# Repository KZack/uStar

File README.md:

# uStar
uStar Files and Documents

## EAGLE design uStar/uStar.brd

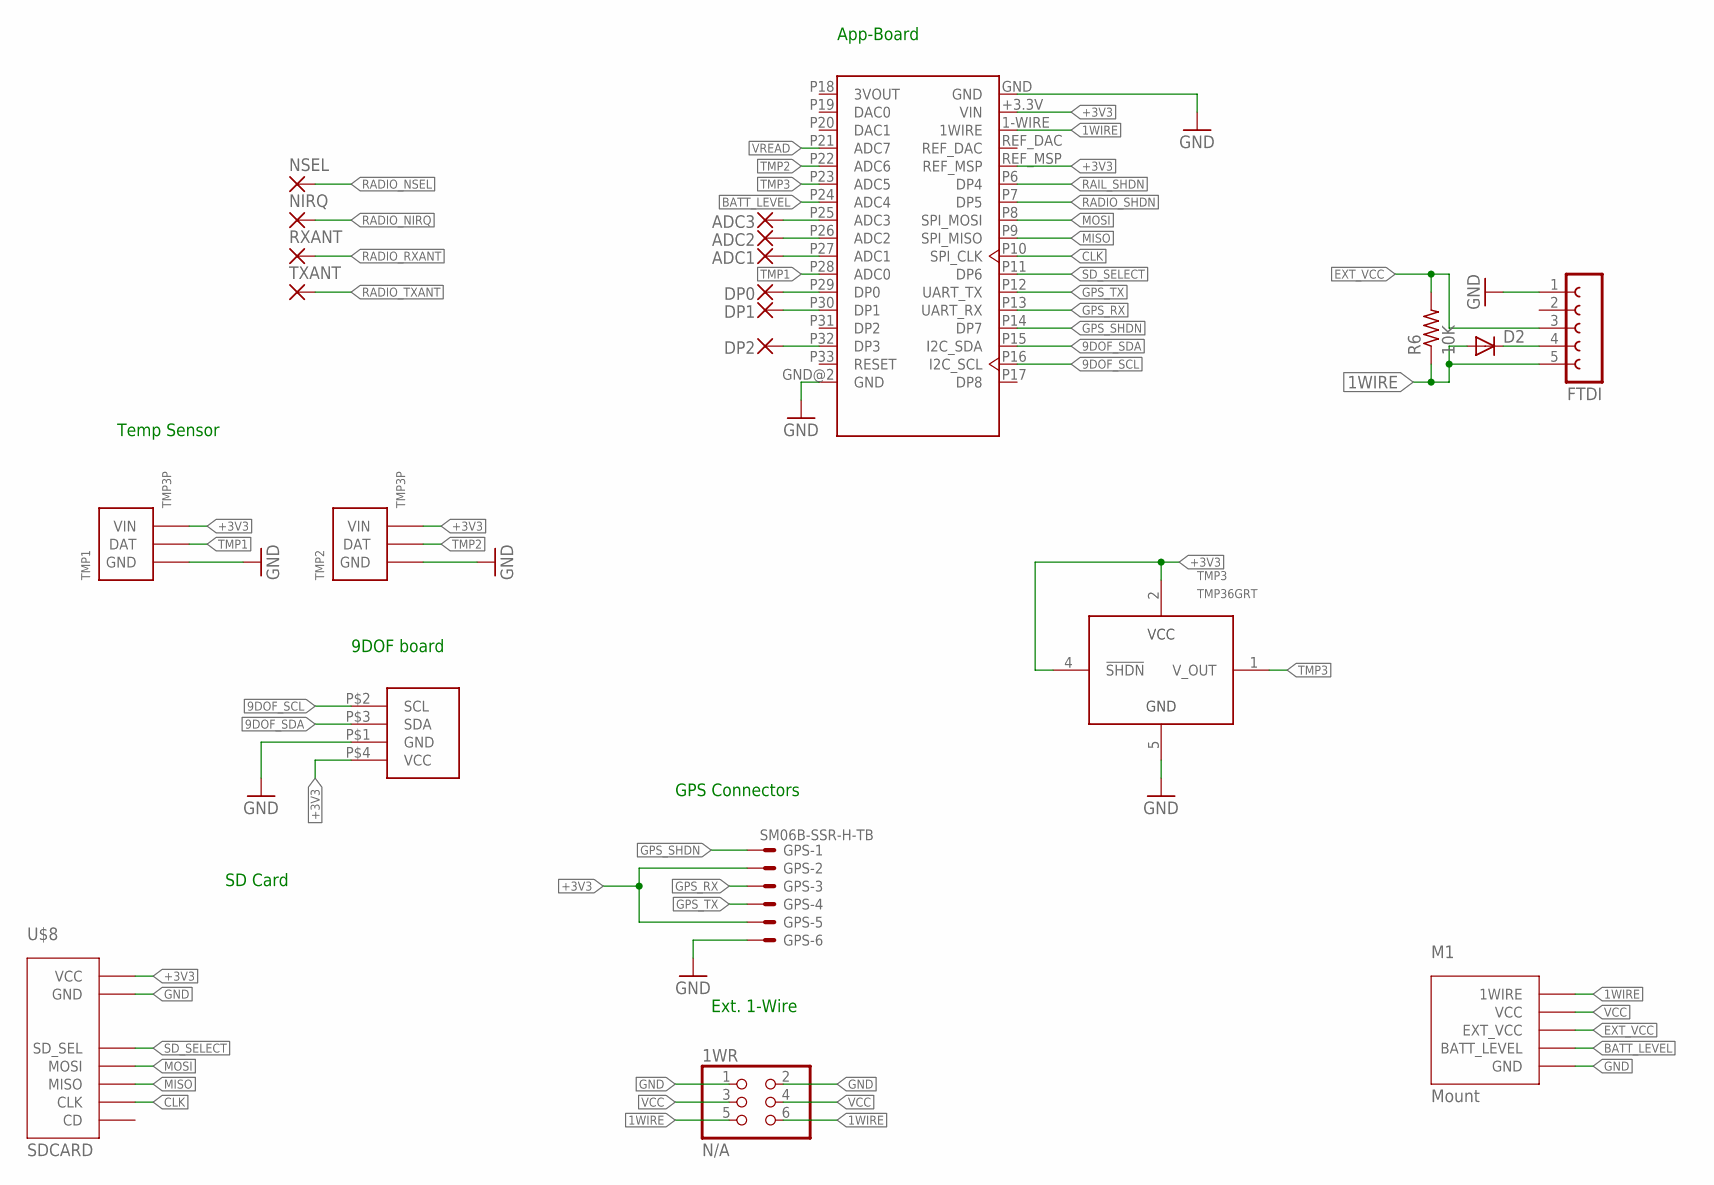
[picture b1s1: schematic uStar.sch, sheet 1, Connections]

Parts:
1WR: N/A; 2X03
ADC1, ADC2, ADC3: 1,6/0,9
D2: D-B260A; SMA-DO214AC
DP0, DP1, DP2: 1,6/0,9
FTDI: FE05-1
GPS: SM06B-SSR-H-TB
M1: Mount; 4X8MOUNT
NIRQ: 1,6/0,9
NSEL: 1,6/0,9
R6: 10K; R0603
RXANT: 1,6/0,9
TMP1, TMP2: TMP3P
TMP3: TMP36GRT; SOT-23-5
TXANT: 1,6/0,9
U$1: App-Board 1.2/1.3; APPCORE_RECEIVER
U$5: 9DOF
U$8: SDCARD

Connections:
1WIRE: 1WR.5, 1WR.6, D2.A, FTDI.5, M1.P$2 (1WIRE), M1.P$5 (1WIRE), R6.1, U$1.1-WIRE (1WIRE)
9DOF_SCL: U$1.P16 (I2C_SCL), U$5.P$2 (SCL)
9DOF_SDA: U$1.P15 (I2C_SDA), U$5.P$3 (SDA)
+3V3: GPS.2, GPS.5, TMP1.P$3 (VIN), TMP2.P$3 (VIN), TMP3.2 (VCC), TMP3.4 (!SHDN), U$1.+3.3V (VIN), U$1.REF_MSP, U$5.P$4 (VCC), U$8.P$3 (VCC); also elsewhere on the board
BATT_LEVEL: M1.P$6 (BATT_LEVEL), U$1.P24 (ADC4)
CLK: U$1.P10 (SPI_CLK), U$8.P$4 (CLK); also elsewhere on the board
EXT_VCC: FTDI.3, M1.P$3 (EXT_VCC), R6.2; also elsewhere on the board
GND: 1WR.1, 1WR.2, FTDI.1, GPS.6, M1.P$1 (GND), M1.P$8 (GND), TMP1.P$1 (GND), TMP2.P$1 (GND), TMP3.5 (GND), U$1.GND, U$1.GND@2 (GND), U$5.P$1 (GND), U$8.P$5 (GND); also elsewhere on the board
GPS_RX: GPS.3, U$1.P13 (UART_RX)
GPS_SHDN: GPS.1, U$1.P14 (DP7)
GPS_TX: GPS.4, U$1.P12 (UART_TX)
MISO: U$1.P9 (SPI_MISO), U$8.P$6 (MISO); also elsewhere on the board
MOSI: U$1.P8 (SPI_MOSI), U$8.P$2 (MOSI); also elsewhere on the board
unnamed: D2.K (C), FTDI.4
unnamed: ADC1.1, U$1.P27 (ADC1)
unnamed: ADC2.1, U$1.P26 (ADC2)
unnamed: ADC3.1, U$1.P25 (ADC3)
unnamed: DP0.1, U$1.P29 (DP0)
unnamed: DP1.1, U$1.P30 (DP1)
unnamed: DP2.1, U$1.P32 (DP3)
RADIO_NIRQ: NIRQ.1; also elsewhere on the board
RADIO_NSEL: NSEL.1; also elsewhere on the board
RADIO_RXANT: RXANT.1; also elsewhere on the board
RADIO_SHDN: U$1.P7 (DP5); also elsewhere on the board
RADIO_TXANT: TXANT.1; also elsewhere on the board
RAIL_SHDN: U$1.P6 (DP4); also elsewhere on the board
SD_SELECT: U$1.P11 (DP6), U$8.P$1 (SD_SEL)
TMP1: TMP1.P$2 (DAT), U$1.P28 (ADC0)
TMP2: TMP2.P$2 (DAT), U$1.P22 (ADC6)
TMP3: TMP3.1 (V_OUT), U$1.P23 (ADC5)
VCC: 1WR.3, 1WR.4, M1.P$4 (VCC), M1.P$7 (VCC); also elsewhere on the board
VREAD: U$1.P21 (ADC7); also elsewhere on the board

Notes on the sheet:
Ext. 1-Wire
App-Board
Temp Sensor
9DOF board
GPS Connectors
SD Card

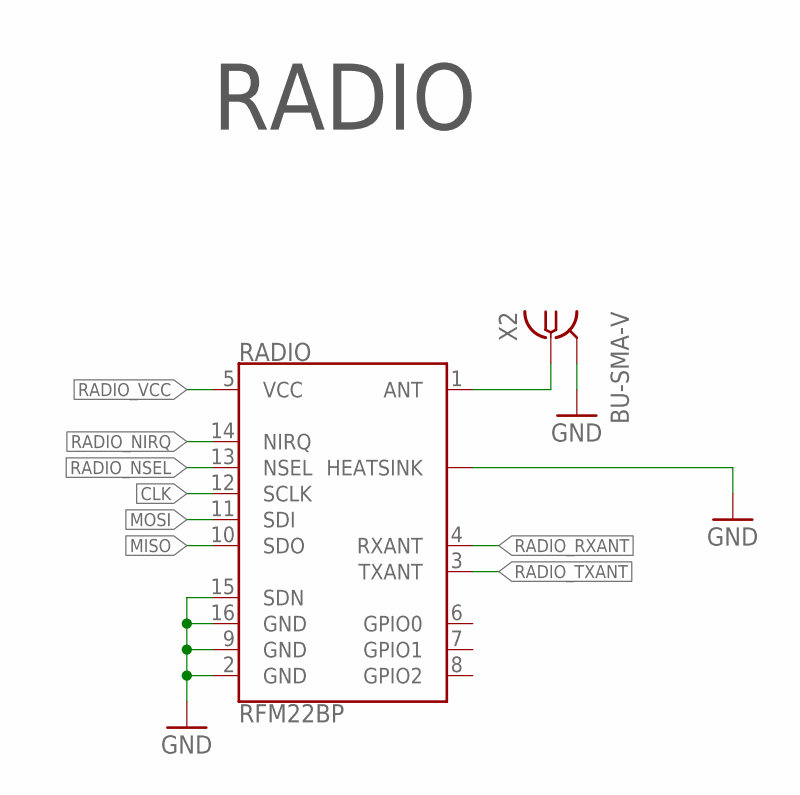
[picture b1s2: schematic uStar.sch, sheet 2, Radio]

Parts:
RADIO: RFM22BP
X2: BU-SMA-V

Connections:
ANT: RADIO.1 (ANT), X2.1
CLK: RADIO.12 (SCLK); also elsewhere on the board
GND: RADIO.2 (GND), RADIO.9 (GND), RADIO.15 (SDN), RADIO.16 (GND), RADIO.P$1 (HEATSINK), X2.2, X2.3 (2), X2.4 (2), X2.5 (2); also elsewhere on the board
MISO: RADIO.10 (SDO); also elsewhere on the board
MOSI: RADIO.11 (SDI); also elsewhere on the board
RADIO_NIRQ: RADIO.14 (NIRQ); also elsewhere on the board
RADIO_NSEL: RADIO.13 (NSEL); also elsewhere on the board
RADIO_RXANT: RADIO.4 (RXANT); also elsewhere on the board
RADIO_TXANT: RADIO.3 (TXANT); also elsewhere on the board
RADIO_VCC: RADIO.5 (VCC); also elsewhere on the board

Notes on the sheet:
RADIO

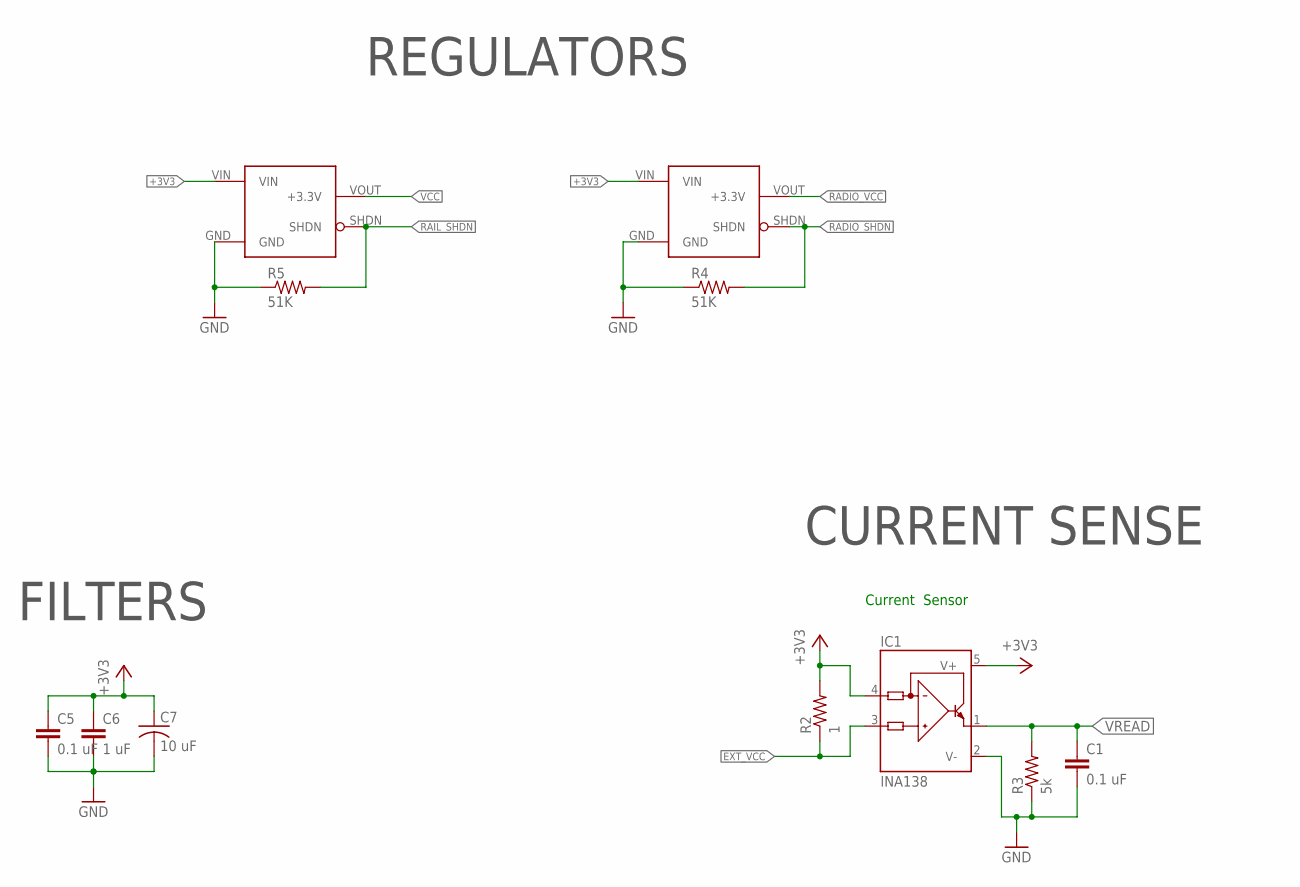
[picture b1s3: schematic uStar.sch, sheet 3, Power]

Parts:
C1, C5: 0.1 uF; C0603
C6: 1 uF; C0603
C7: 10 uF; C0805_POL
IC1: INA138; SOT23-5
R2: 1; R0603
R3: 5k; R0603
R4, R5: 51K; R0603
U$3, U$7: S7V8F3_VOLT_REG-3V3_1AHORZ-DOWN; S7V_DOWN

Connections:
+3V3: C5.1, C6.1, C7.2 (1), IC1.4 (IN-), IC1.5 (V+), R2.2, U$3.VIN, U$7.VIN; also elsewhere on the board
EXT_VCC: IC1.3 (IN+), R2.1; also elsewhere on the board
GND: C1.2, C5.2, C6.2, C7.1 (2), IC1.2 (V-), R3.1, R4.1, R5.1, U$3.GND, U$7.GND; also elsewhere on the board
RADIO_SHDN: R4.2, U$7.SHDN; also elsewhere on the board
RADIO_VCC: U$7.VOUT (+3.3V); also elsewhere on the board
RAIL_SHDN: R5.2, U$3.SHDN; also elsewhere on the board
VCC: U$3.VOUT (+3.3V); also elsewhere on the board
VREAD: C1.1, IC1.1 (OUT), R3.2; also elsewhere on the board

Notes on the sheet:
Current Sensor
REGULATORS
CURRENT SENSE
FILTERS

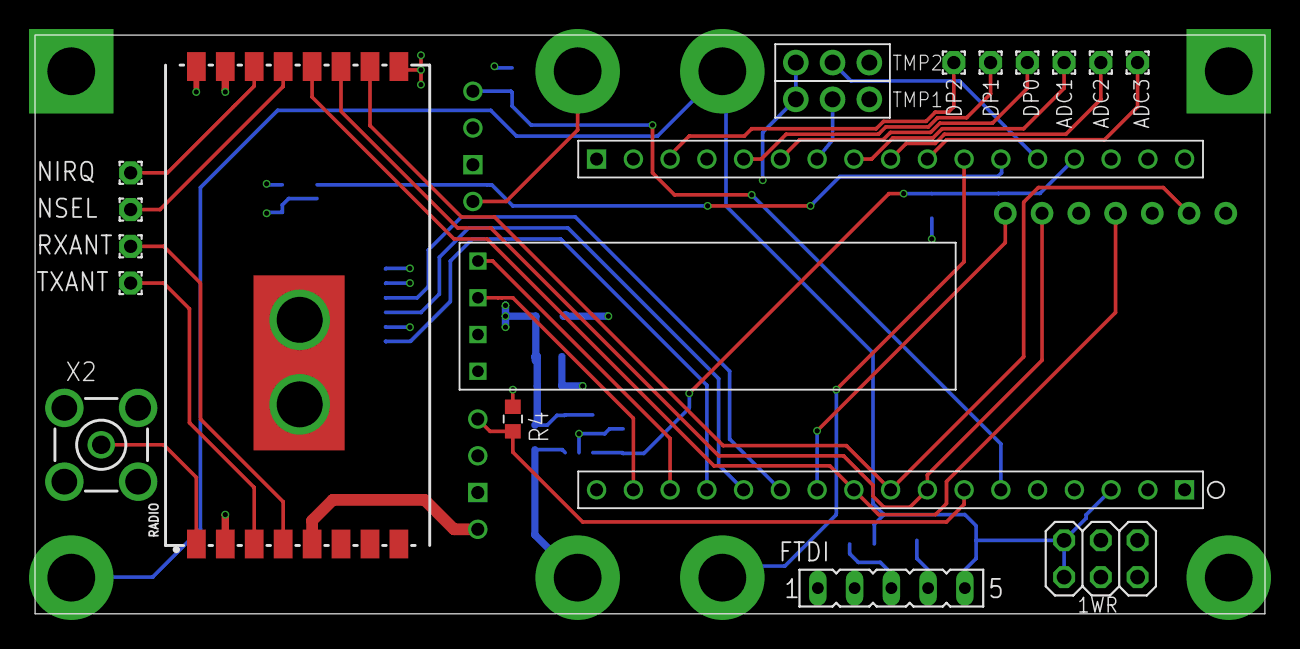
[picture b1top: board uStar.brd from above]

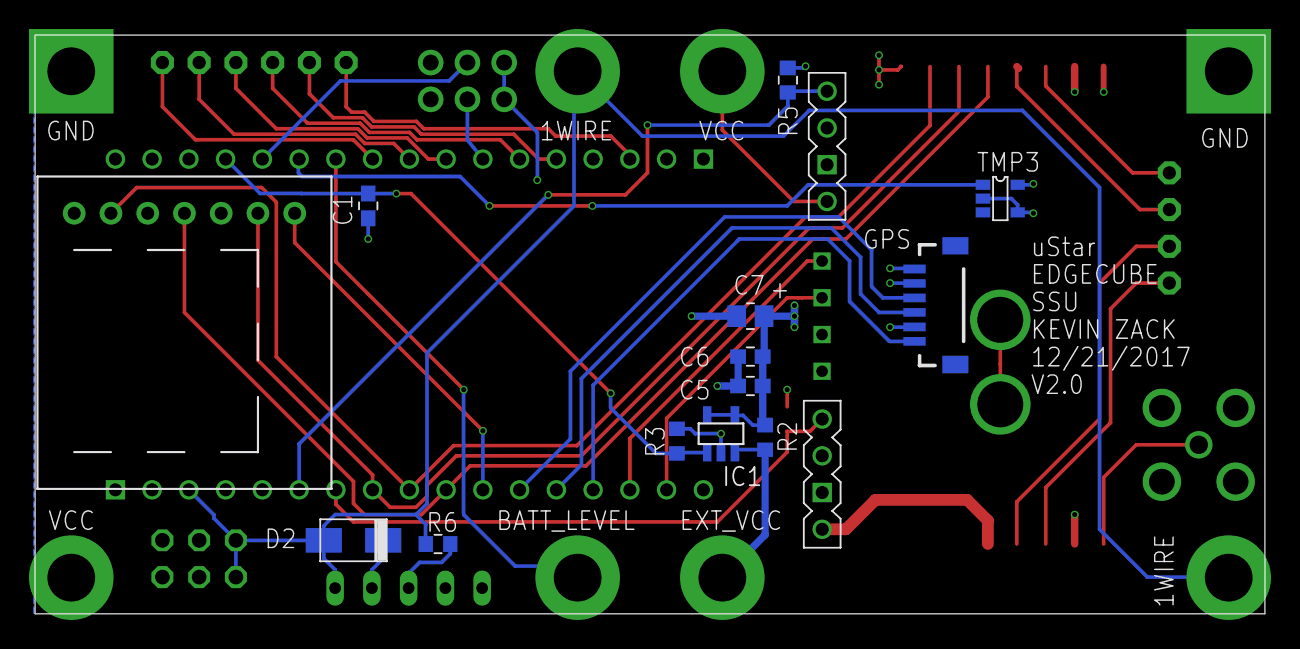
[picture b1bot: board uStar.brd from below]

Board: 4 copper layers, 85.0 x 40.0 mm, 35 parts (14 on the bottom side), 34 nets.

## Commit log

2018-01-04 Add files via upload
    uStar v2.0 with 4 layer board. Also assembly guide
